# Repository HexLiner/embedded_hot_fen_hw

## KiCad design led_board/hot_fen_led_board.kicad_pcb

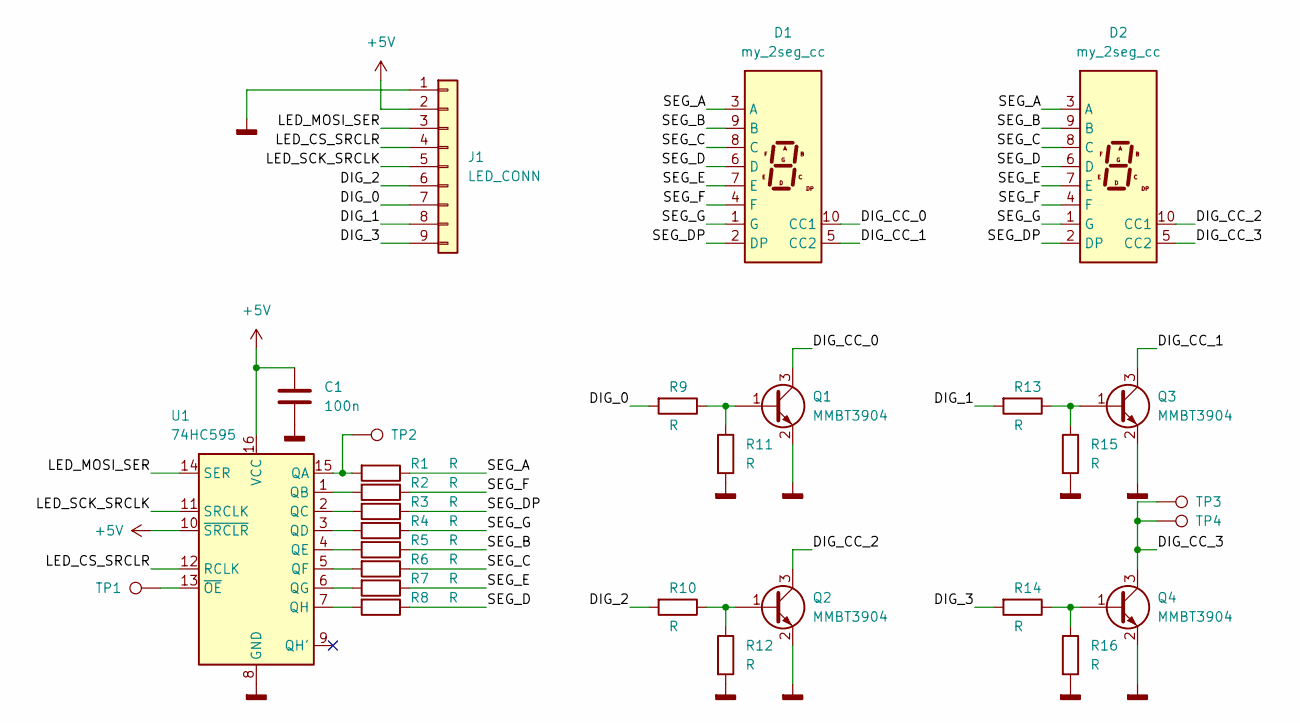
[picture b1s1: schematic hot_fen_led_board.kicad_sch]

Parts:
C1: 100n; C_0805_2012Metric
D1, D2: my_2seg_cc
J1: LED_CONN; my_9pin_SMD_conn
Q1, Q2, Q3, Q4: MMBT3904; SOT-23
R1, R2, R3, R4, R5, R6, R7, R8, R9, R10, R11, R12, R13, R14, R15, R16: R; R_0805_2012Metric
TP1, TP2, TP3, TP4: TestPoint; TestPoint_Pad_D1.0mm
U1: 74HC595; SO-16_3.9x9.9mm_P1.27mm

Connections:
+5V: C1.1, J1.2, U1.10 (~SRCLR), U1.16 (VCC)
/DIG_0: J1.7, R9.2
/DIG_1: J1.8, R13.2
/DIG_2: J1.6, R10.2
/DIG_3: J1.9, R14.2
/DIG_CC_0: D1.10 (CC1), Q1.3 (C)
/DIG_CC_1: D1.5 (CC2), Q3.3 (C)
/DIG_CC_2: D2.10 (CC1), Q2.3 (C)
/DIG_CC_3: D2.5 (CC2), Q4.3 (C), TP3.1, TP4.1
/LED_CS_SRCLR: J1.4, U1.12 (RCLK)
/LED_MOSI_SER: J1.3, U1.14 (SER)
/LED_SCK_SRCLK: J1.5, U1.11 (SRCLK)
/SEG_A: D1.3 (A), D2.3 (A), R1.1
/SEG_B: D1.9 (B), D2.9 (B), R5.1
/SEG_C: D1.8 (C), D2.8 (C), R6.1
/SEG_D: D1.6 (D), D2.6 (D), R8.1
/SEG_DP: D1.2 (DP), D2.2 (DP), R3.1
/SEG_E: D1.7 (E), D2.7 (E), R7.1
/SEG_F: D1.4 (F), D2.4 (F), R2.1
/SEG_G: D1.1 (G), D2.1 (G), R4.1
GNDD: C1.2, J1.1, Q1.2 (E), Q2.2 (E), Q3.2 (E), Q4.2 (E), R11.2, R12.2, R15.2, R16.2, U1.8 (GND)
unnamed: Q1.1 (B), R9.1, R11.1
unnamed: Q2.1 (B), R10.1, R12.1
unnamed: Q3.1 (B), R13.1, R15.1
unnamed: Q4.1 (B), R14.1, R16.1
unnamed: R1.2, TP2.1, U1.15 (QA)
unnamed: R2.2, U1.1 (QB)
unnamed: R3.2, U1.2 (QC)
unnamed: R4.2, U1.3 (QD)
unnamed: R5.2, U1.4 (QE)
unnamed: R6.2, U1.5 (QF)
unnamed: R7.2, U1.6 (QG)
unnamed: R8.2, U1.7 (QH)
unnamed: TP1.1, U1.13 (~OE)

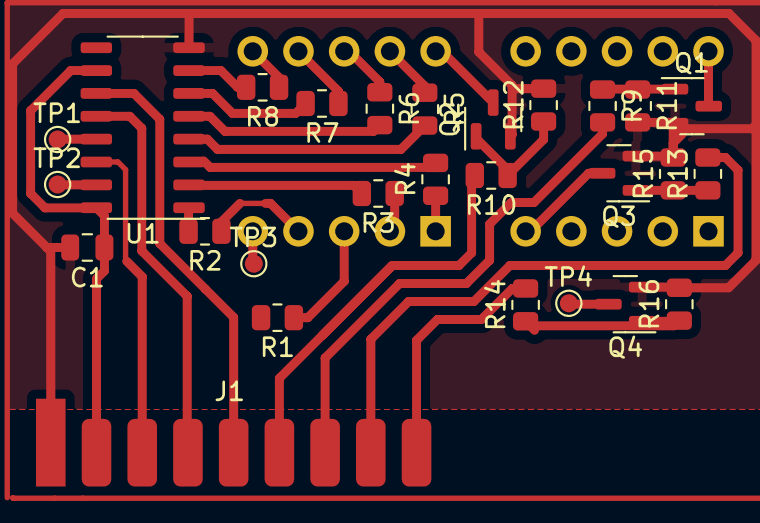
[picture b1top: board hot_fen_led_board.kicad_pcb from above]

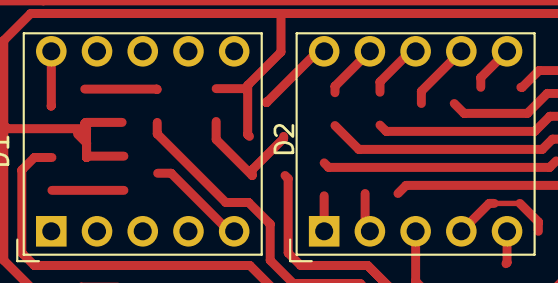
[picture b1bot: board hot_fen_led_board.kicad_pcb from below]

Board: 2 copper layers, 29 parts (2 on the bottom side), 34 nets.

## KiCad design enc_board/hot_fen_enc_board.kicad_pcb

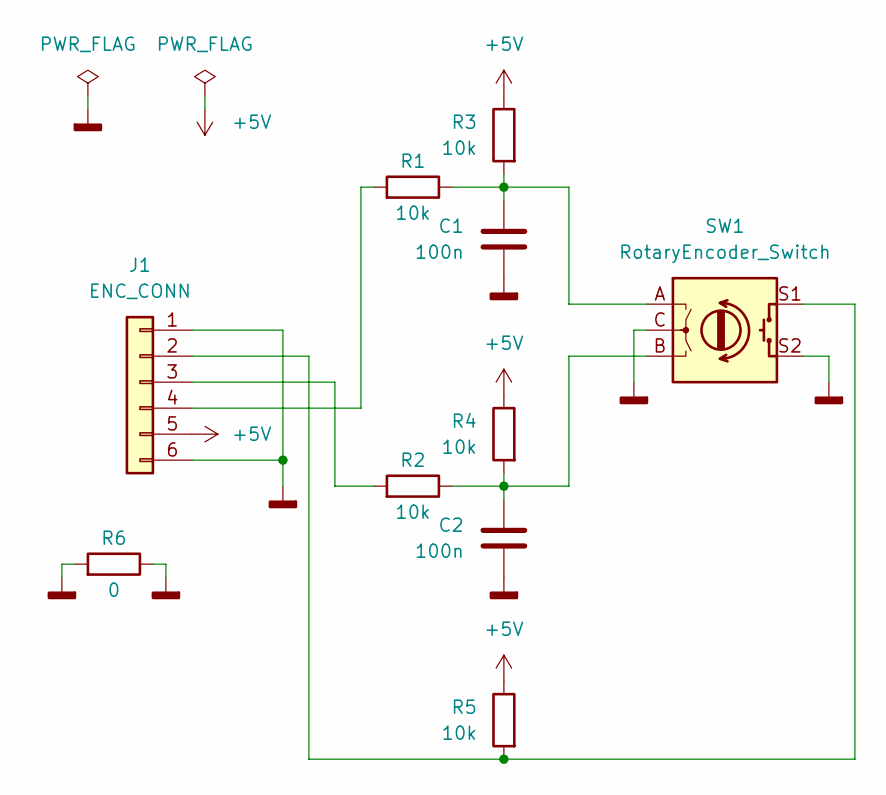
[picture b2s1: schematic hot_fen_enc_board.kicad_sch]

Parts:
C1, C2: 100n; C_0805_2012Metric
J1: ENC_CONN; PinHeader_1x06_P2.54mm_Vertical
R1, R2, R3, R4, R5: 10k; R_0805_2012Metric
R6: 0; R_1206_3216Metric
SW1: RotaryEncoder_Switch; RotaryEncoder_Alps_EC11E-Switch_Vertical_H20mm

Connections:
+5V: J1.5, R3.1, R4.1, R5.1
GNDD: C1.2, C2.2, J1.1, J1.6, R6.1, R6.2, SW1.C, SW1.S2
unnamed: C1.1, R1.1, R3.2, SW1.A
unnamed: C2.1, R2.1, R4.2, SW1.B
unnamed: J1.2, R5.2, SW1.S1
unnamed: J1.3, R2.2
unnamed: J1.4, R1.2

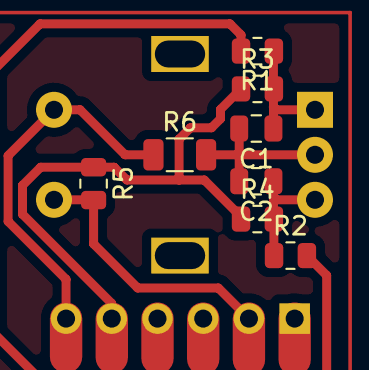
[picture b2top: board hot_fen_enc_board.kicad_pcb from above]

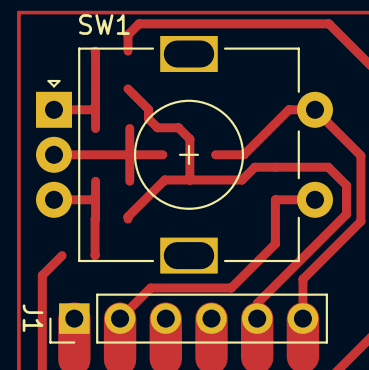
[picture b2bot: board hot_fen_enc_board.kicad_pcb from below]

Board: 2 copper layers, 10 parts (2 on the bottom side), 7 nets.

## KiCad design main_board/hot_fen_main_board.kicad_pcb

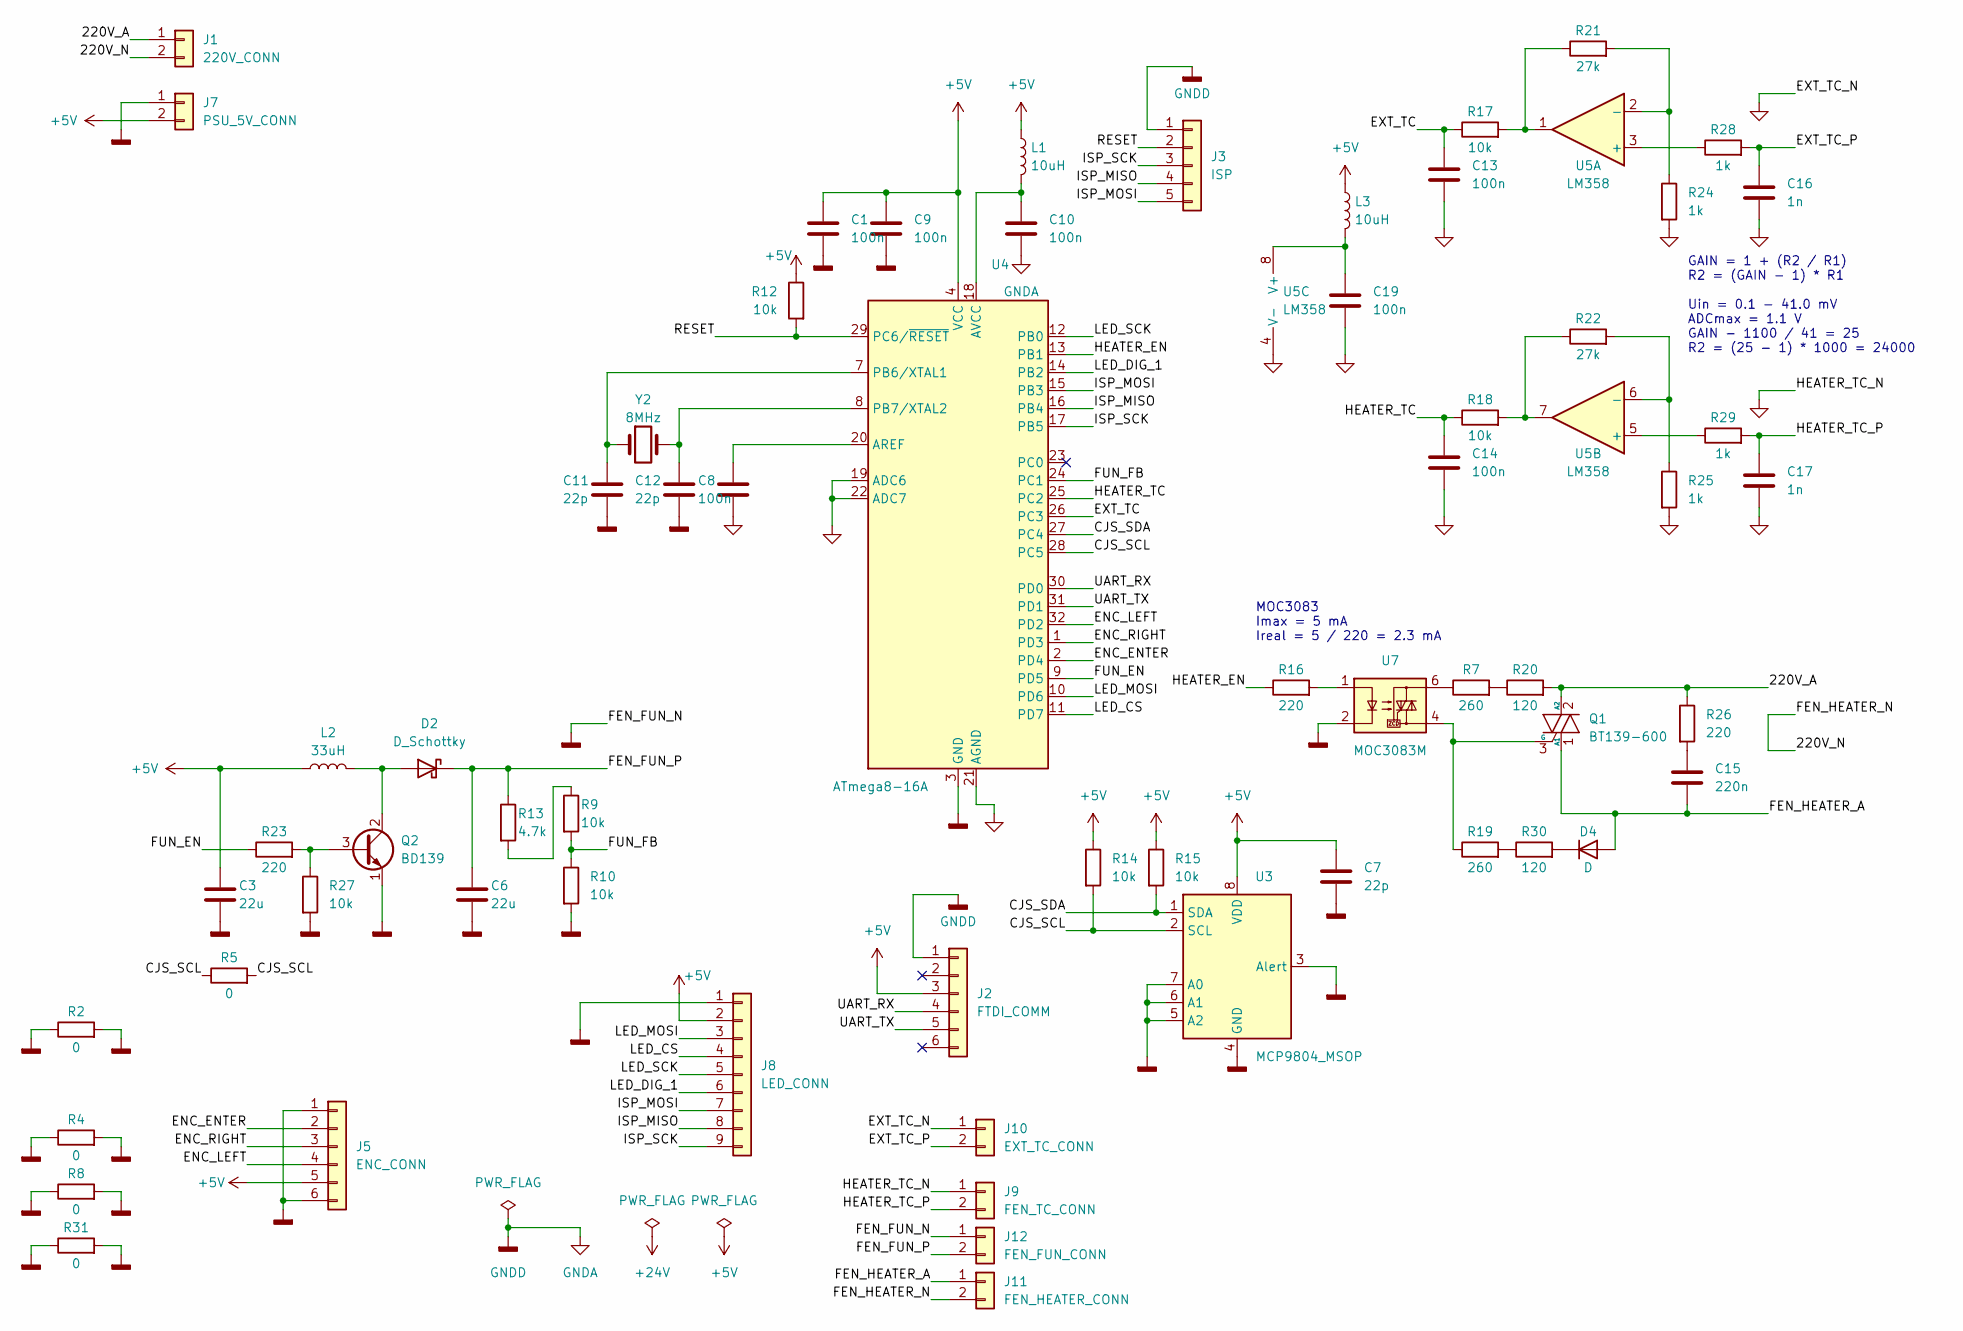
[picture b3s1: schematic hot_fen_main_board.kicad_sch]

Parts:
C1, C8, C9, C10, C13, C14, C19: 100n; C_0805_2012Metric
C3: 22u; C_1206_3216Metric
C6: 22u; C_Radial_D8.0mm_H7.0mm_P3.50mm
C7, C11, C12: 22p; C_0805_2012Metric
C15: 220n; C_Axial_L12.0mm_D6.5mm_P15.00mm_Horizontal
C16, C17: 1n; C_0805_2012Metric
D2: D_Schottky; D_SMA
D4: D; D_SMA_Handsoldering
J1: 220V_CONN; my_220v_conn
J2: FTDI_COMM; PinSocket_1x06_P2.54mm_Vertical
J3: ISP; PinSocket_1x05_P2.54mm_Vertical
J5: ENC_CONN; PinHeader_1x06_P2.54mm_Vertical
J7: PSU_5V_CONN; my_2pin_DIP_conn
J8: LED_CONN; my_9pin_SMD_conn
J9: FEN_TC_CONN; my_2pin_SMD_conn
J10: EXT_TC_CONN; my_2pin_SMD_conn
J11: FEN_HEATER_CONN; my_220v_conn
J12: FEN_FUN_CONN; my_2pin_SMD_conn
L1: 10uH; L_0805_2012Metric
L2: 33uH; L_12x12mm_H4.5mm
L3: 10uH; L_Axial_L7.0mm_D3.3mm_P12.70mm_Horizontal_Fastron_MICC
Q1: BT139-600; my_TO-220
Q2: BD139; TO-126-3_Vertical
R2, R4, R5, R8, R31: 0; R_1206_3216Metric
R7, R19: 260; R_0805_2012Metric
R9, R10, R12, R17, R18, R27: 10k; R_0805_2012Metric
R13: 4.7k; R_0805_2012Metric
R14, R15: 10k; R_0603_1608Metric
R16, R23: 220; R_0805_2012Metric
R20, R30: 120; R_0805_2012Metric
R21, R22: 27k; R_0805_2012Metric
R24: 1k; R_1206_3216Metric
R25, R28, R29: 1k; R_0805_2012Metric
R26: 220; R_Axial_DIN0414_L11.9mm_D4.5mm_P15.24mm_Horizontal
U3: MCP9804_MSOP; MSOP-8_3x3mm_P0.65mm
U4: ATmega8-16A; TQFP-32_7x7mm_P0.8mm
U5: LM358; SOIC-8_3.9x4.9mm_P1.27mm
U7: MOC3083M; DIP-6_W7.62mm
Y2: 8MHz; Crystal_HC18-U_Vertical

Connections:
+5V: C1.1, C3.1, C7.1, C9.1, J2.3, J5.5, J7.2, J8.2, L1.1, L2.1, L3.1, R12.1, R14.1, R15.1, U3.8 (VDD), U4.4 (VCC), U4.6 (VCC)
/220V_A: J1.1, Q1.2 (A2), R20.2, R26.1
/220V_N: J1.2, J11.2
/CJS_SCL: R5.1, R5.2, R14.2, U3.2 (SCL), U4.28 (PC5)
/CJS_SDA: R15.2, U3.1 (SDA), U4.27 (PC4)
/ENC_ENTER: J5.2, U4.2 (PD4)
/ENC_LEFT: J5.4, U4.32 (PD2)
/ENC_RIGHT: J5.3, U4.1 (PD3)
/EXT_TC: C13.1, R17.1, U4.26 (PC3)
/EXT_TC_P: C16.1, J10.2, R28.2
/FEN_FUN_P: C6.1, D2.1 (K), J12.2, R13.1
/FEN_HEATER_A: C15.2, D4.2 (A), J11.1, Q1.1 (A1)
/FUN_EN: R23.1, U4.9 (PD5)
/FUN_FB: R9.2, R10.1, U4.24 (PC1)
/HEATER_EN: R16.1, U4.13 (PB1)
/HEATER_TC: C14.1, R18.1, U4.25 (PC2)
/HEATER_TC_P: C17.1, J9.2, R29.2
/ISP_MISO: J3.4, J8.8, U4.16 (PB4)
/ISP_MOSI: J3.5, J8.7, U4.15 (PB3)
/ISP_SCK: J3.3, J8.9, U4.17 (PB5)
/LED_CS: J8.4, U4.11 (PD7)
/LED_DIG_1: J8.6, U4.14 (PB2)
/LED_MOSI: J8.3, U4.10 (PD6)
/LED_SCK: J8.5, U4.12 (PB0)
/RESET: J3.2, R12.2, U4.29 (PC6/~RESET)
/UART_RX: J2.4, U4.30 (PD0)
/UART_TX: J2.5, U4.31 (PD1)
GNDA: C1.2, C3.2, C6.2, C7.2, C8.2, C9.2, C10.2, C11.2, C12.2, C13.2, C14.2, C16.2, C17.2, C19.2, J2.1, J3.1, J5.1, J5.6, J7.1, J8.1, J9.1, J10.1, J12.1, Q2.1 (E), R2.1, R2.2, R4.1, R4.2, R8.1, R8.2, R10.2, R24.2, R25.2, R27.2, R31.1, R31.2, U3.3 (Alert), U3.4 (GND), U3.5 (A2), U3.6 (A1), U3.7 (A0), U4.3 (GND), U4.5 (GND), U4.19 (ADC6), U4.21 (AGND), U4.22 (ADC7), U5.4 (V-), U7.2
unnamed: C8.1, U4.20 (AREF)
unnamed: C10.1, L1.2, U4.18 (AVCC)
unnamed: C11.1, U4.7 (PB6/XTAL1), Y2.1
unnamed: C12.1, U4.8 (PB7/XTAL2), Y2.2
unnamed: C15.1, R26.2
unnamed: C19.1, L3.2, U5.8 (V+)
unnamed: D2.2 (A), L2.2, Q2.2 (C)
unnamed: D4.1 (K), R30.2
unnamed: Q2.3 (B), R23.2, R27.1
unnamed: R9.1, R13.2
unnamed: R16.2, U7.1
unnamed: R17.2, R21.1, U5.1
unnamed: R18.2, R22.1, U5.7
unnamed: R19.2, R30.1
unnamed: R7.2, R20.1
unnamed: R21.2, R24.1, U5.2 (-)
unnamed: R22.2, R25.1, U5.6 (-)
unnamed: R28.1, U5.3 (+)
unnamed: R29.1, U5.5 (+)
unnamed: Q1.3 (G), R19.1, U7.4
unnamed: R7.1, U7.6

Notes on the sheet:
GAIN = 1 + (R2 / R1) R2 = (GAIN - 1) * R1 Uin = 0.1 - 41.0 mV ADCmax = 1.1 V GAIN - 1100 / 41 = 25 R2 = (25 - 1) * 1000 = 24000
MOC3083 Imax = 5 mA Ireal = 5 / 220 = 2.3 mA

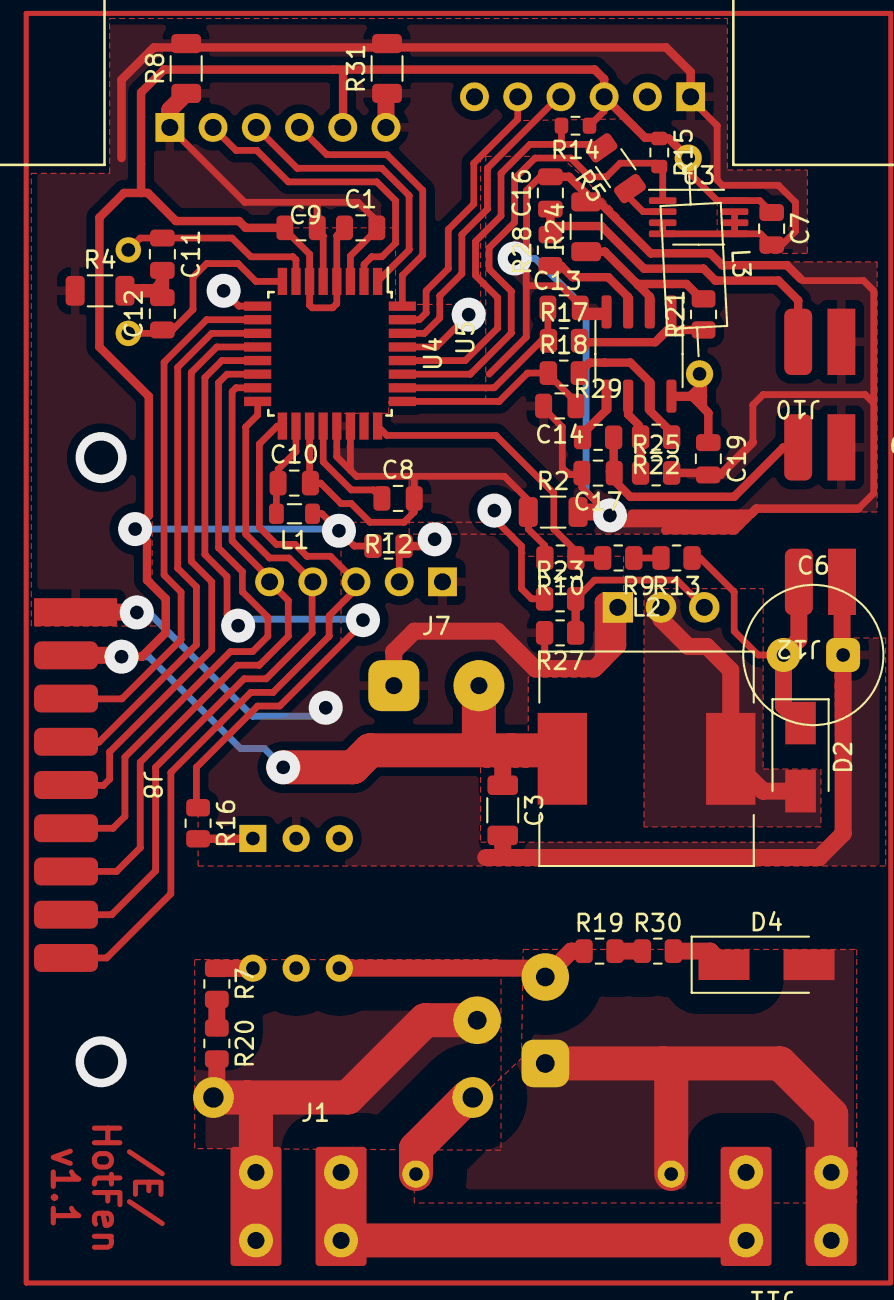
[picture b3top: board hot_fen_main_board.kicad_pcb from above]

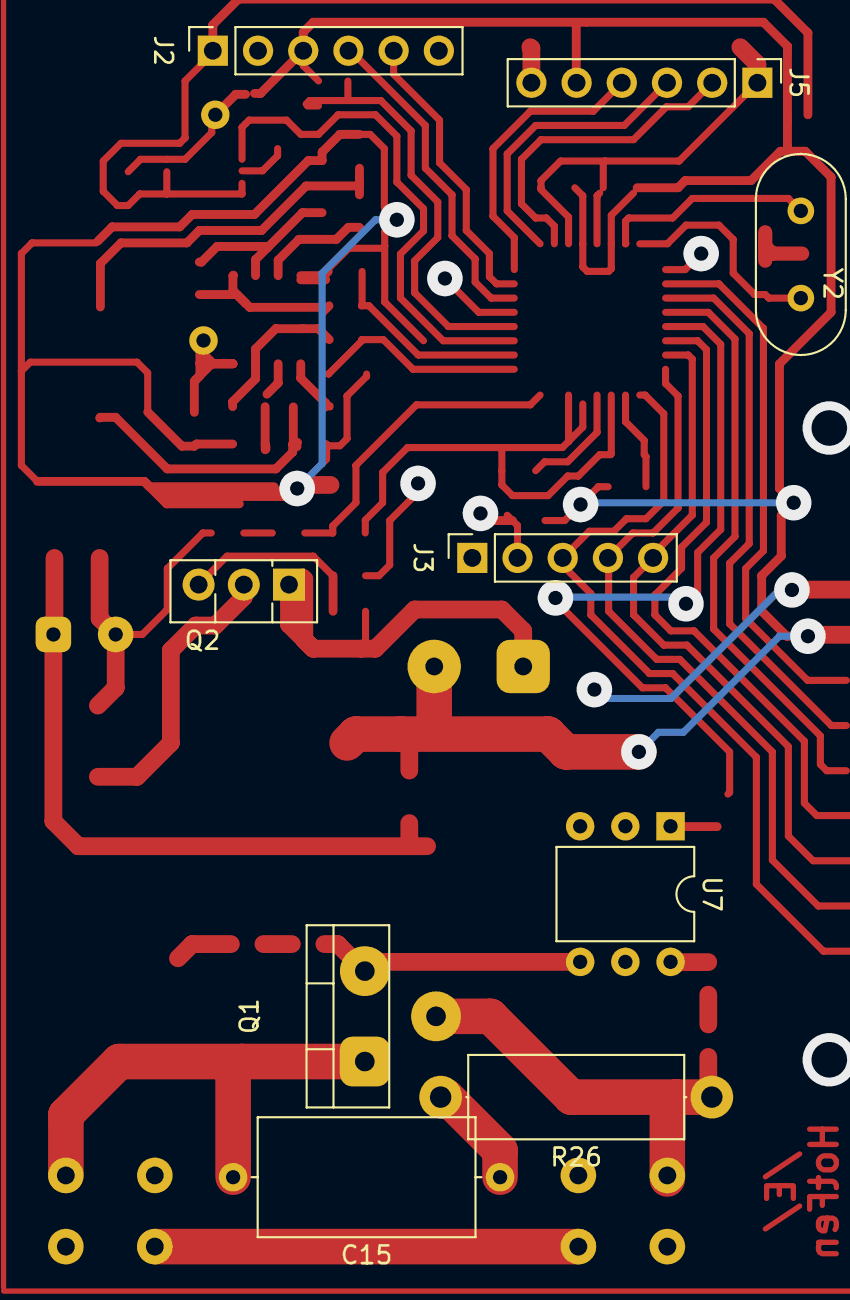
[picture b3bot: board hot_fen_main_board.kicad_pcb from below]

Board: 2 copper layers, 64 parts (9 on the bottom side), 49 nets.

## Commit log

2025-03-05 Initial
